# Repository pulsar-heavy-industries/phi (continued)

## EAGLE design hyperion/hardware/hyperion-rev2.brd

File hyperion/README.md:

# Hyperion

This repository contains the source code, Ableton remote script and hardware design for the Pulsar Heavy Industries Hyperion module.

Each Hyperion module provides you with:
* Fader.
* 2 Pressable rotary encoders.
* 7 Pots with center detent.
* 8 LED-lit pushbuttons - 2 blue and 6 red/green(/orange).
* 2 color OLED display.
* Standard PHI CANBUS connectivity.
* A powerful [STM32F405](http://www.st.com/en/microcontrollers/stm32f405-415.html?querycriteria=productId=LN1035) microcontroller.
* 10 segment (7 green + 3 red) LED bar graph.

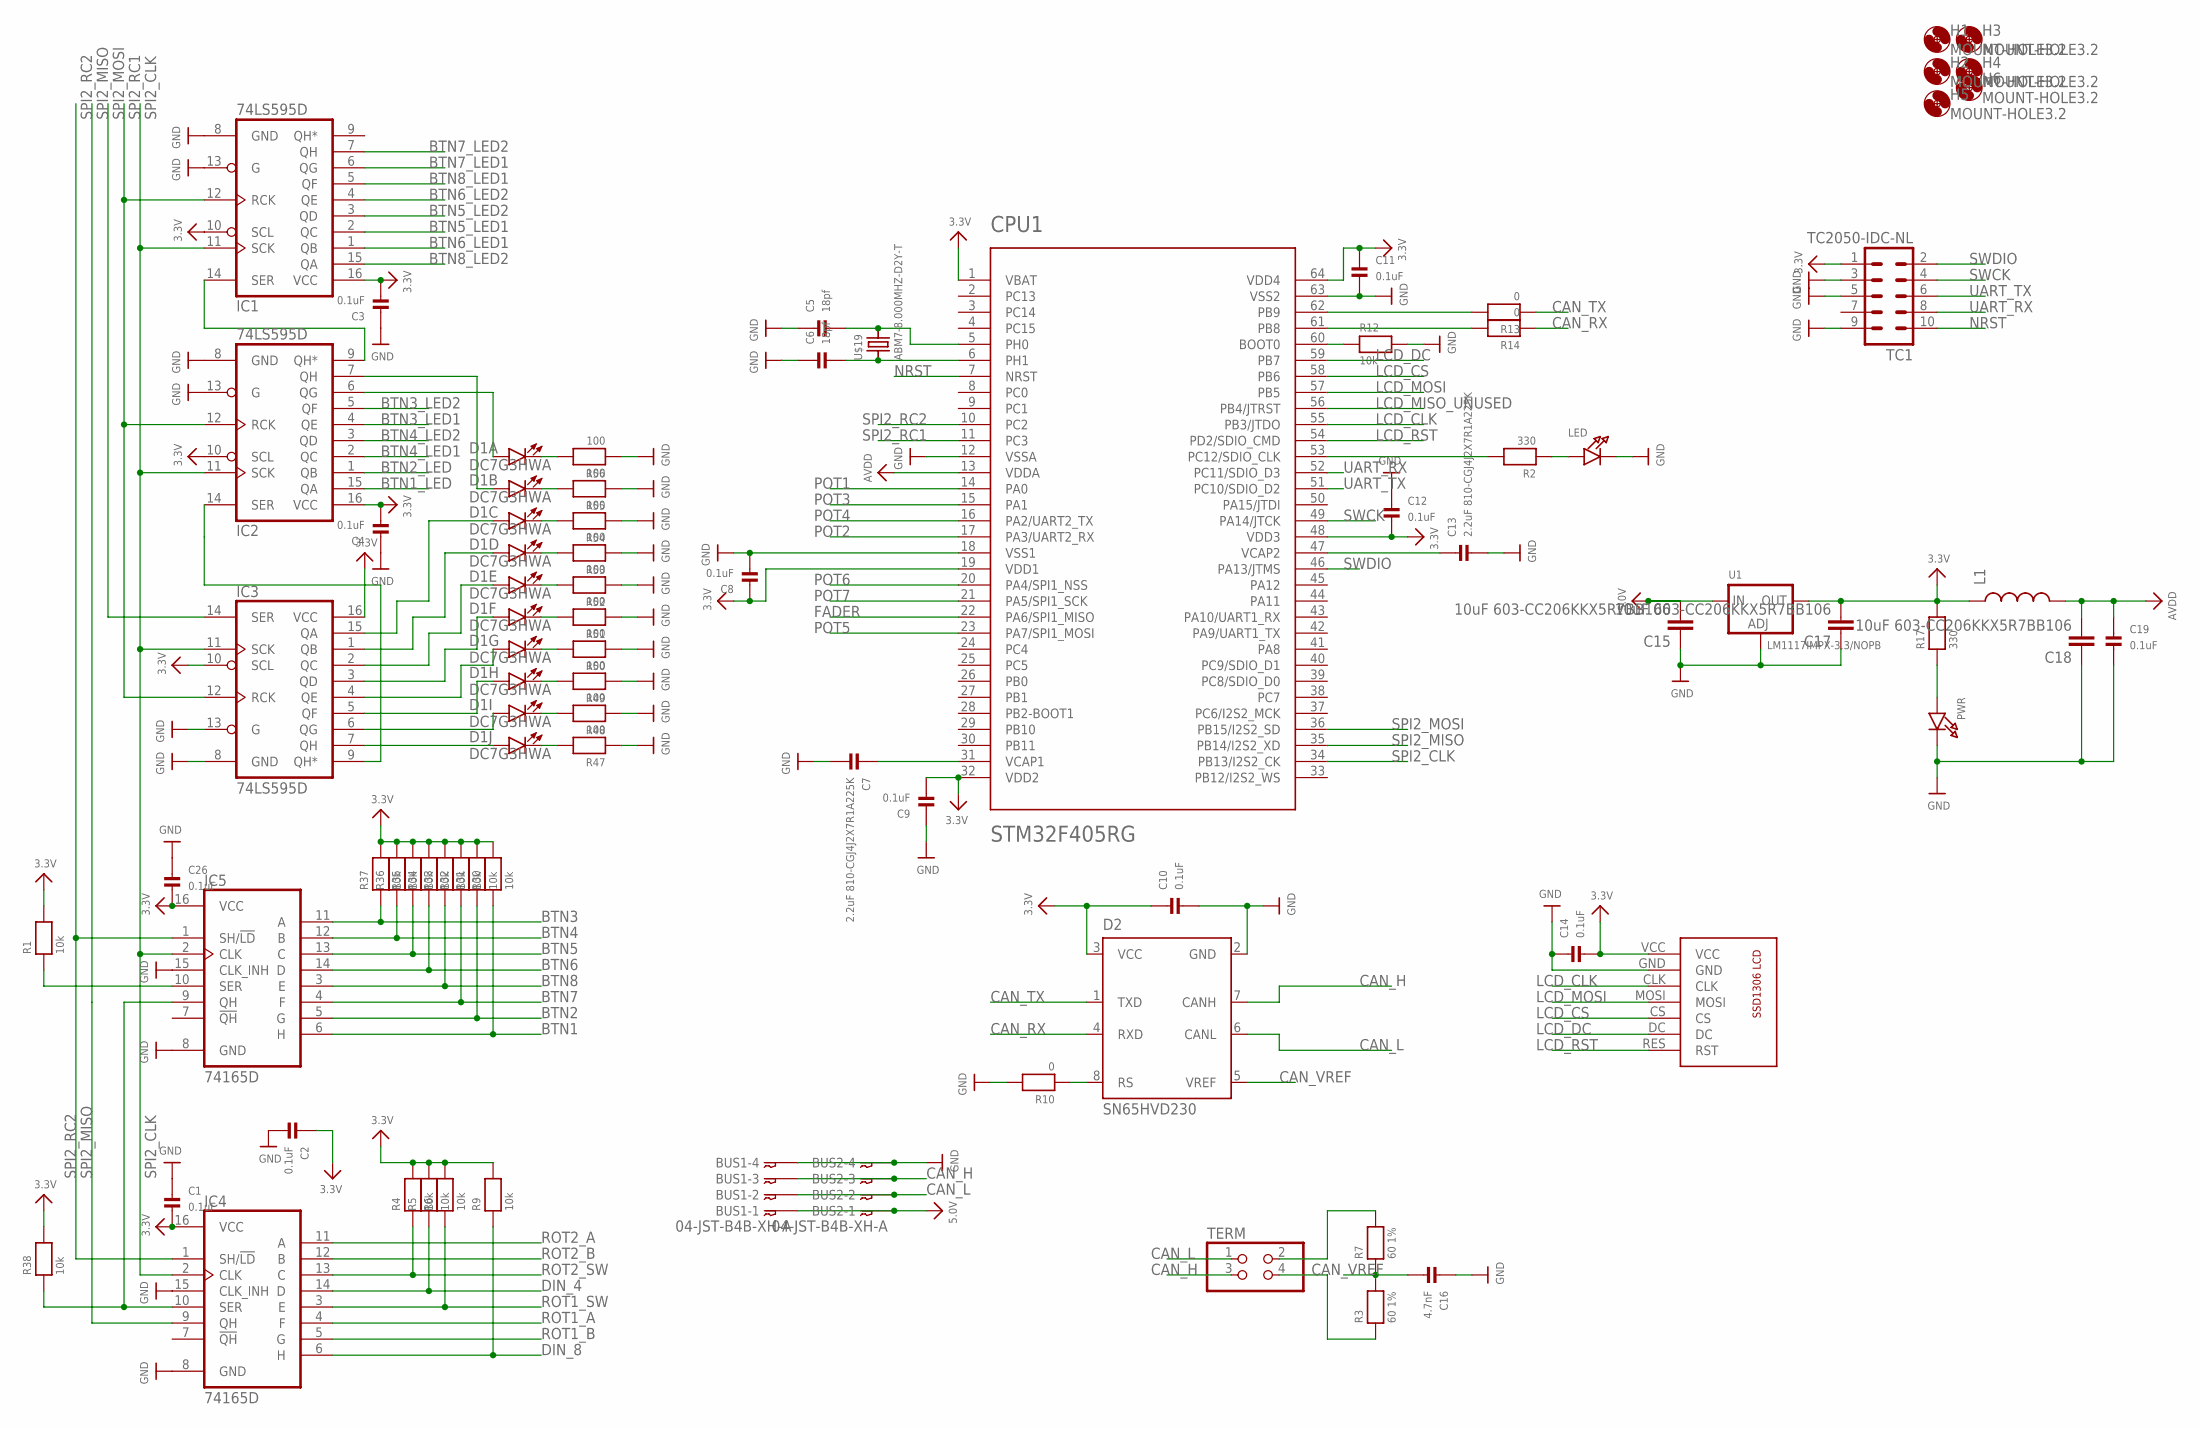
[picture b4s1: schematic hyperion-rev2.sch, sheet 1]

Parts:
BUS1, BUS2: 04-JST-B4B-XH-A; B4B-XH
C1, C2, C3, C4, C8, C9, C10, C11, C12, C14, C19, C26: 0.1uF; 0603
C5, C6: 18pf; 0603
C7, C13: 2.2uF 810-CGJ4J2X7R1A225K; 0805; MPN CGJ4J2X7R1A225K125AA
C15, C17, C18: 10uF 603-CC206KKX5R7BB106; 1206; MPN CC1206KKX5R7BB106
C16: 4.7nF; 0603
CPU1: STM32F405RG; TQFP64; MPN STM32F405RGT6
D1: DC7G3HWA; LED_BARGAPH_10
D2: SN65HVD230; SO8
H1, H2, H3, H4, H5, H6: MOUNT-HOLE3.2; 3,2
IC1, IC2, IC3: 74LS595D; SO16
IC4, IC5: 74165D; SO16
L1: INDUCTOR0805; 0805; MPN 2508056017Y2
LCD: SSD1306-7PINWITHOUT-HOLES; SSD1306-7PIN-NO-HOLES
LED: LED0603; CHIPLED_0603
PWR: LED0603; CHIPLED_0603
R1, R4, R5, R6, R9, R12, R30, R31, R32, R33, R34, R35, R36, R37, R38: 10k; _0603
R2, R17: 330; 0603
R3, R7: 60 1%; 0603; MPN MF-RES-0603-60.4
R10, R13, R14: 0; _0603
R47, R48, R49, R50, R51, R52, R53, R54, R55, R56: 100; _0603
TC1: TC2050-IDC-NL
TERM: PINHD-2X2; 2X02
U1: LM1117IMPX-3.3/NOPB; SOT223-R
U$19: ABM7-8.000MHZ-D2Y-T

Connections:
3.3V: C1.2, C2.1, C3.2, C4.2, C8.1, C9.2, C10.1, C11.1, C12.2, C14.2, C17.2, C26.2, CPU1.1 (VBAT), CPU1.19 (VDD1), CPU1.32 (VDD2), CPU1.48 (VDD3), CPU1.64 (VDD4), D2.3 (VCC), IC1.10 (SCL), IC1.16 (VCC), IC2.10 (SCL), IC2.16 (VCC), IC3.10 (SCL), IC3.16 (VCC), IC4.16 (VCC), IC5.16 (VCC), L1.1, LCD.VCC, R1.2, R4.2, R5.2, R6.2, R9.2, R17.2, R30.2, R31.2, R32.2, R33.2, R34.2, R35.2, R36.2, R37.2, R38.2, TC1.1, U1.2 (OUT); also elsewhere on the board
5.0V: BUS1.P$1, BUS2.P$1, C15.2, U1.3 (IN); also elsewhere on the board
AVDD: C18.2, C19.1, CPU1.13 (VDDA), L1.2
BTN1: IC5.6 (H), R30.1; also elsewhere on the board
BTN1_LED: IC2.15 (QA); also elsewhere on the board
BTN2: IC5.5 (G), R31.1; also elsewhere on the board
BTN2_LED: IC2.1 (QB); also elsewhere on the board
BTN3: IC5.11 (A), R37.1; also elsewhere on the board
BTN3_LED1: IC2.4 (QE); also elsewhere on the board
BTN3_LED2: IC2.5 (QF); also elsewhere on the board
BTN4: IC5.12 (B), R36.1; also elsewhere on the board
BTN4_LED1: IC2.2 (QC); also elsewhere on the board
BTN4_LED2: IC2.3 (QD); also elsewhere on the board
BTN5: IC5.13 (C), R35.1; also elsewhere on the board
BTN5_LED1: IC1.2 (QC); also elsewhere on the board
BTN5_LED2: IC1.3 (QD); also elsewhere on the board
BTN6: IC5.14 (D), R34.1; also elsewhere on the board
BTN6_LED1: IC1.1 (QB); also elsewhere on the board
BTN6_LED2: IC1.4 (QE); also elsewhere on the board
BTN7: IC5.4 (F), R32.1; also elsewhere on the board
BTN7_LED1: IC1.6 (QG); also elsewhere on the board
BTN7_LED2: IC1.7 (QH); also elsewhere on the board
BTN8: IC5.3 (E), R33.1; also elsewhere on the board
BTN8_LED1: IC1.5 (QF); also elsewhere on the board
BTN8_LED2: IC1.15 (QA); also elsewhere on the board
CAN_H: BUS1.P$3, BUS2.P$3, D2.7 (CANH), TERM.3
CAN_L: BUS1.P$2, BUS2.P$2, D2.6 (CANL), TERM.1
CAN_RX: D2.4 (RXD), R14.1
CAN_TX: D2.1 (TXD), R13.1
CAN_VREF: C16.2, D2.5 (VREF), R3.2, R7.1
DIN_4: IC4.14 (D), R5.1
DIN_8: IC4.6 (H), R9.1
FADER: CPU1.22 (PA6/SPI1_MISO); also elsewhere on the board
GND: BUS1.P$4, BUS2.P$4, C1.1, C2.2, C3.1, C4.1, C5.1, C6.1, C7.2, C8.2, C9.1, C10.2, C11.2, C12.1, C13.2, C14.1, C15.1, C16.1, C17.1, C18.1, C19.2, C26.1, CPU1.12 (VSSA), CPU1.18 (VSS1), CPU1.63 (VSS2), D2.2 (GND), IC1.8 (GND), IC1.13 (G), IC2.8 (GND), IC2.13 (G), IC3.8 (GND), IC3.13 (G), IC4.8 (GND), IC4.15 (CLK_INH), IC5.8 (GND), IC5.15 (CLK_INH), LCD.GND, LED.C, PWR.C, R10.2, R12.2, R47.1, R48.1, R49.1, R50.1, R51.1, R52.1, R53.1, R54.1, R55.1, R56.1, TC1.3, TC1.5, TC1.9, U1.1 (ADJ); also elsewhere on the board
LCD_CLK: CPU1.55 (PB3/JTDO), LCD.CLK
LCD_CS: CPU1.58 (PB6), LCD.CS
LCD_DC: CPU1.59 (PB7), LCD.DC
LCD_MISO_UNUSED: CPU1.56 (PB4/JTRST)
LCD_MOSI: CPU1.57 (PB5), LCD.MOSI
LCD_RST: CPU1.54 (PD2/SDIO_CMD), LCD.RES (RST)
unnamed: C6.2, CPU1.6 (PH1), U$19.P$1 (1)
unnamed: C5.2, CPU1.5 (PH0), U$19.P$2 (2)
unnamed: C13.1, CPU1.47 (VCAP2)
unnamed: C7.1, CPU1.31 (VCAP1)
unnamed: PWR.A, R17.1
unnamed: CPU1.60 (BOOT0), R12.1
unnamed: D1.5 (A), IC3.2 (QC)
unnamed: D1.2 (A), IC2.7 (QH)
unnamed: D1.1 (A), IC2.6 (QG)
unnamed: IC1.14 (SER), IC2.9 (QH*)
unnamed: CPU1.62 (PB9), R13.2
unnamed: D1.11 (C), R47.2
unnamed: D1.12 (C), R48.2
unnamed: D1.13 (C), R49.2
unnamed: D1.14 (C), R50.2
unnamed: D1.15 (C), R51.2
unnamed: D1.16 (C), R52.2
unnamed: D1.17 (C), R53.2
unnamed: D1.18 (C), R54.2
unnamed: D1.19 (C), R55.2
unnamed: D1.20 (C), R56.2
unnamed: IC4.10 (SER), IC5.9 (QH), R38.1
unnamed: CPU1.61 (PB8), R14.2
unnamed: IC5.10 (SER), R1.1
unnamed: LED.A, R2.1
unnamed: D1.10 (A), IC3.7 (QH)
unnamed: D1.9 (A), IC3.6 (QG)
unnamed: D1.8 (A), IC3.5 (QF)
unnamed: CPU1.53 (PC12/SDIO_CLK), R2.2
unnamed: R7.2, TERM.2
unnamed: R3.1, TERM.4
unnamed: D1.7 (A), IC3.4 (QE)
unnamed: D1.6 (A), IC3.3 (QD)
unnamed: D1.4 (A), IC3.1 (QB)
unnamed: D1.3 (A), IC3.15 (QA)
unnamed: IC2.14 (SER), IC3.9 (QH*)
unnamed: D2.8 (RS), R10.1
NRST: CPU1.7 (NRST), TC1.10
POT1: CPU1.14 (PA0); also elsewhere on the board
POT2: CPU1.17 (PA3/UART2_RX); also elsewhere on the board
POT3: CPU1.15 (PA1); also elsewhere on the board
POT4: CPU1.16 (PA2/UART2_TX); also elsewhere on the board
POT5: CPU1.23 (PA7/SPI1_MOSI); also elsewhere on the board
POT6: CPU1.20 (PA4/SPI1_NSS); also elsewhere on the board
POT7: CPU1.21 (PA5/SPI1_SCK); also elsewhere on the board
ROT1_A: IC4.4 (F); also elsewhere on the board
ROT1_B: IC4.5 (G); also elsewhere on the board
ROT1_SW: IC4.3 (E), R6.1; also elsewhere on the board
ROT2_A: IC4.11 (A); also elsewhere on the board
ROT2_B: IC4.12 (B); also elsewhere on the board
ROT2_SW: IC4.13 (C), R4.1; also elsewhere on the board
SPI2_CLK: CPU1.34 (PB13/I2S2_CK), IC1.11 (SCK), IC2.11 (SCK), IC3.11 (SCK), IC4.2 (CLK), IC5.2 (CLK)
SPI2_MISO: CPU1.35 (PB14/I2S2_XD), IC4.9 (QH)
SPI2_MOSI: CPU1.36 (PB15/I2S2_SD), IC3.14 (SER)
SPI2_RC1: CPU1.11 (PC3), IC1.12 (RCK), IC2.12 (RCK), IC3.12 (RCK)
SPI2_RC2: CPU1.10 (PC2), IC4.1 (SH/!LD), IC5.1 (SH/!LD)
SWCK: CPU1.49 (PA14/JTCK), TC1.4
SWDIO: CPU1.46 (PA13/JTMS), TC1.2
UART_RX: CPU1.52 (PC11/SDIO_D3), TC1.8
UART_TX: CPU1.51 (PC10/SDIO_D2), TC1.6

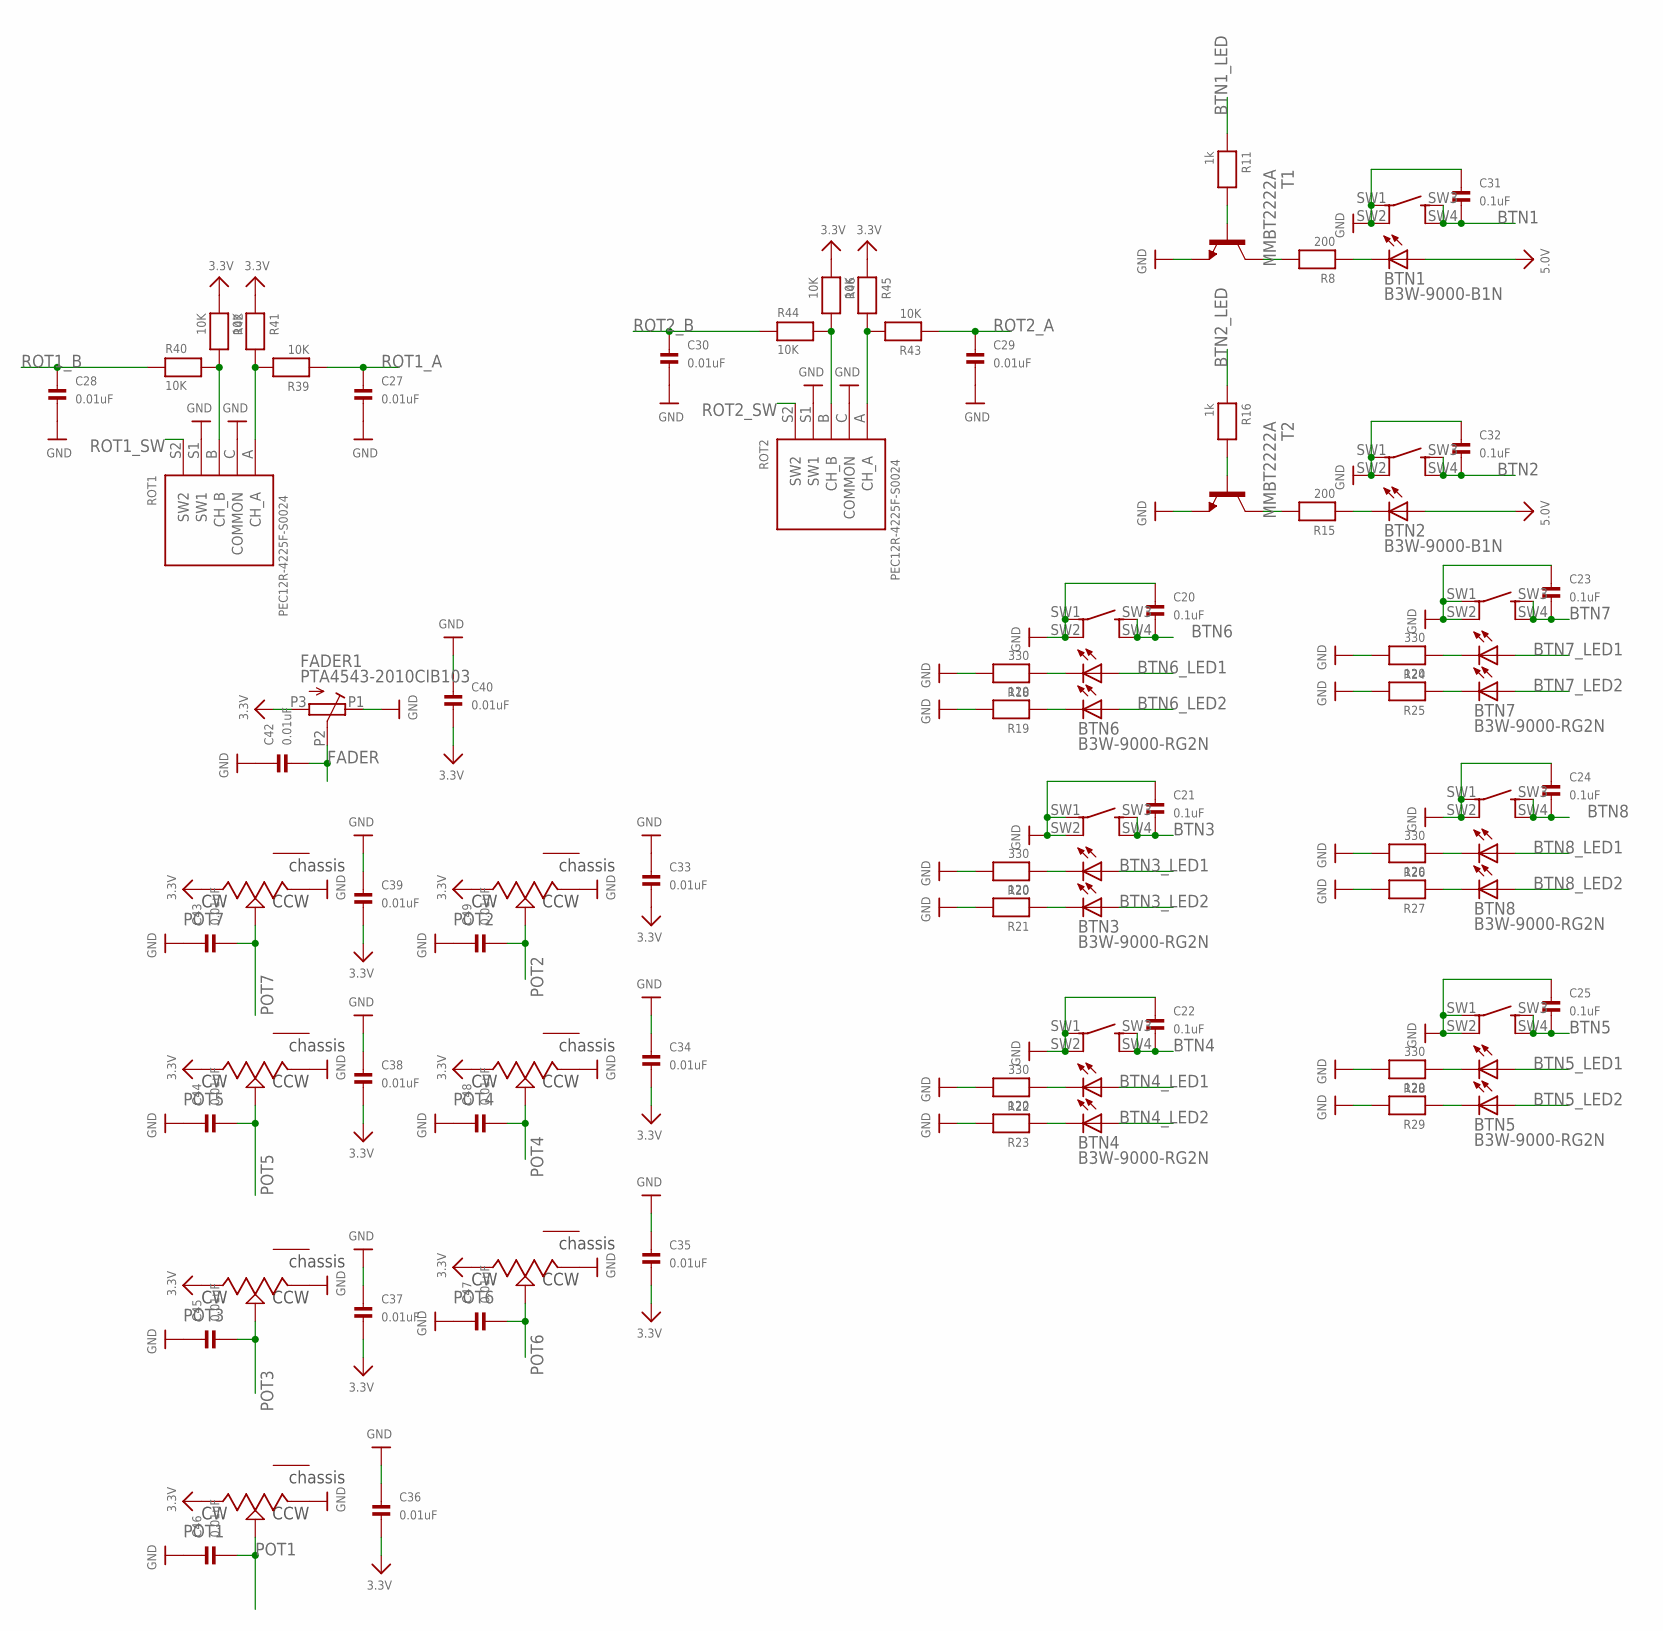
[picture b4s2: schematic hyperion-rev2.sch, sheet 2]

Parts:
BTN1, BTN2: B3W-9000-B1N; B3W-9000-X1X
BTN3, BTN4, BTN5, BTN6, BTN7, BTN8: B3W-9000-RG2N; B3W-9000-X2X
C20, C21, C22, C23, C24, C25, C31, C32: 0.1uF; 0603
C27, C28, C29, C30, C33, C34, C35, C36, C37, C38, C39, C40, C42, C43, C44, C45, C46, C47, C48, C49: 0.01uF; 0603
FADER1: PTA4543-2010CIB103; PTA4543-2015CPB103
POT1, POT2, POT3, POT4, POT5, POT6, POT7: POTENTIOMETERPTV09A_VERTICAL; PTV09A-4
R8, R15: 200; 0603
R11, R16: 1k; 0603
R18, R20, R22, R24, R26, R28: 330; 0603
R19, R21, R23, R25, R27, R29: 120; 0603
R39, R40, R41, R42, R43, R44, R45, R46: 10K; 0603
ROT1, ROT2: PEC12R-4225F-S0024; PEC111-4XXXK-SXXXX
T1, T2: MMBT2222A; SOT23-BEC

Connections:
3.3V: C33.2, C34.2, C35.2, C36.2, C37.2, C38.2, C39.2, C40.2, FADER1.P3 (E), POT1.CW, POT2.CW, POT3.CW, POT4.CW, POT5.CW, POT6.CW, POT7.CW, R41.1, R42.1, R45.1, R46.1; also elsewhere on the board
5.0V: BTN1.LED1+, BTN2.LED1+; also elsewhere on the board
BTN1: BTN1.SW3 (SW2_A), BTN1.SW4 (SW2_B), C31.2; also elsewhere on the board
BTN1_LED: R11.1; also elsewhere on the board
BTN2: BTN2.SW3 (SW2_A), BTN2.SW4 (SW2_B), C32.2; also elsewhere on the board
BTN2_LED: R16.1; also elsewhere on the board
BTN3: BTN3.SW3 (SW2_A), BTN3.SW4 (SW2_B), C21.2; also elsewhere on the board
BTN3_LED1: BTN3.LED1+; also elsewhere on the board
BTN3_LED2: BTN3.LED2+; also elsewhere on the board
BTN4: BTN4.SW3 (SW2_A), BTN4.SW4 (SW2_B), C22.2; also elsewhere on the board
BTN4_LED1: BTN4.LED1+; also elsewhere on the board
BTN4_LED2: BTN4.LED2+; also elsewhere on the board
BTN5: BTN5.SW3 (SW2_A), BTN5.SW4 (SW2_B), C25.2; also elsewhere on the board
BTN5_LED1: BTN5.LED1+; also elsewhere on the board
BTN5_LED2: BTN5.LED2+; also elsewhere on the board
BTN6: BTN6.SW3 (SW2_A), BTN6.SW4 (SW2_B), C20.2; also elsewhere on the board
BTN6_LED1: BTN6.LED1+; also elsewhere on the board
BTN6_LED2: BTN6.LED2+; also elsewhere on the board
BTN7: BTN7.SW3 (SW2_A), BTN7.SW4 (SW2_B), C23.2; also elsewhere on the board
BTN7_LED1: BTN7.LED1+; also elsewhere on the board
BTN7_LED2: BTN7.LED2+; also elsewhere on the board
BTN8: BTN8.SW3 (SW2_A), BTN8.SW4 (SW2_B), C24.2; also elsewhere on the board
BTN8_LED1: BTN8.LED1+; also elsewhere on the board
BTN8_LED2: BTN8.LED2+; also elsewhere on the board
FADER: C42.2, FADER1.P2 (S); also elsewhere on the board
GND: BTN1.SW1 (SW1_A), BTN1.SW2 (SW1_B), BTN2.SW1 (SW1_A), BTN2.SW2 (SW1_B), BTN3.SW1 (SW1_A), BTN3.SW2 (SW1_B), BTN4.SW1 (SW1_A), BTN4.SW2 (SW1_B), BTN5.SW1 (SW1_A), BTN5.SW2 (SW1_B), BTN6.SW1 (SW1_A), BTN6.SW2 (SW1_B), BTN7.SW1 (SW1_A), BTN7.SW2 (SW1_B), BTN8.SW1 (SW1_A), BTN8.SW2 (SW1_B), C20.1, C21.1, C22.1, C23.1, C24.1, C25.1, C27.2, C28.2, C29.2, C30.2, C31.1, C32.1, C33.1, C34.1, C35.1, C36.1, C37.1, C38.1, C39.1, C40.1, C42.1, C43.1, C44.1, C45.1, C46.1, C47.1, C48.1, C49.1, FADER1.P1 (A), POT1.CCW, POT2.CCW, POT3.CCW, POT4.CCW, POT5.CCW, POT6.CCW, POT7.CCW, R18.2, R19.2, R20.2, R21.2, R22.2, R23.2, R24.2, R25.2, R26.2, R27.2, R28.2, R29.2, ROT1.C (COMMON), ROT1.S1 (SW1), ROT2.C (COMMON), ROT2.S1 (SW1), T1.E, T2.E; also elsewhere on the board
unnamed: BTN6.LED1-, R18.1
unnamed: BTN6.LED2-, R19.1
unnamed: BTN3.LED1-, R20.1
unnamed: BTN3.LED2-, R21.1
unnamed: BTN7.LED1-, R24.1
unnamed: BTN7.LED2-, R25.1
unnamed: R40.2, R42.2, ROT1.B (CH_B)
unnamed: R39.2, R41.2, ROT1.A (CH_A)
unnamed: BTN8.LED1-, R26.1
unnamed: BTN8.LED2-, R27.1
unnamed: R44.2, R46.2, ROT2.B (CH_B)
unnamed: R43.2, R45.2, ROT2.A (CH_A)
unnamed: BTN4.LED1-, R22.1
unnamed: BTN4.LED2-, R23.1
unnamed: BTN5.LED1-, R28.1
unnamed: BTN5.LED2-, R29.1
unnamed: BTN2.LED1-, R15.1
unnamed: BTN1.LED1-, R8.1
unnamed: R8.2, T1.C
unnamed: R11.2, T1.B
unnamed: R15.2, T2.C
unnamed: R16.2, T2.B
POT1: C46.2, POT1.CENTER (WIPER); also elsewhere on the board
POT2: C49.2, POT2.CENTER (WIPER); also elsewhere on the board
POT3: C45.2, POT3.CENTER (WIPER); also elsewhere on the board
POT4: C48.2, POT4.CENTER (WIPER); also elsewhere on the board
POT5: C44.2, POT5.CENTER (WIPER); also elsewhere on the board
POT6: C47.2, POT6.CENTER (WIPER); also elsewhere on the board
POT7: C43.2, POT7.CENTER (WIPER); also elsewhere on the board
ROT1_A: C27.1, R39.1; also elsewhere on the board
ROT1_B: C28.1, R40.1; also elsewhere on the board
ROT1_SW: ROT1.S2 (SW2); also elsewhere on the board
ROT2_A: C29.1, R43.1; also elsewhere on the board
ROT2_B: C30.1, R44.1; also elsewhere on the board
ROT2_SW: ROT2.S2 (SW2); also elsewhere on the board

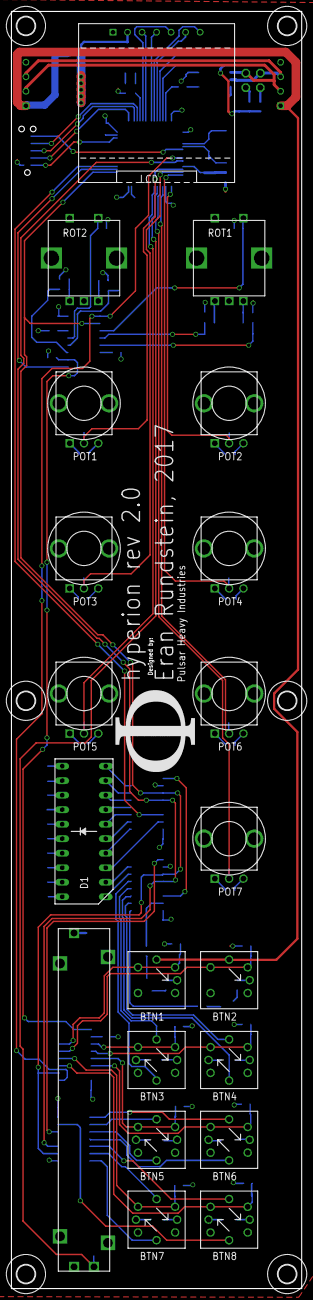
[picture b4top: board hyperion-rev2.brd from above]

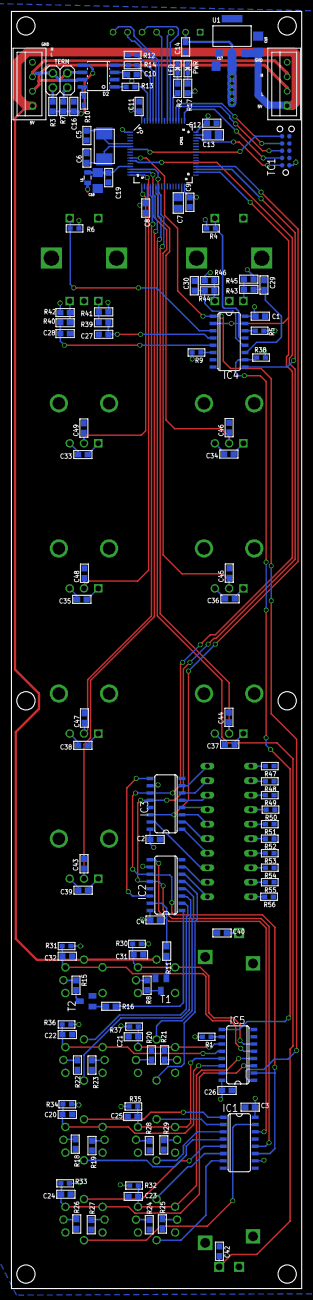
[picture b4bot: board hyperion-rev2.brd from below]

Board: 2 copper layers, 50.8 x 223.5 mm, 148 parts (122 on the bottom side), 121 nets.

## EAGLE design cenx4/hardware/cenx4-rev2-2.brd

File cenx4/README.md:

# Cenx4

This repository contains the source code, Ableton remote script and hardware design for the Pulsar Heavy Industries Cenx4 controller.

The main features are (some of which are already fully implemented):
- Easy to use: Automatic mapping of selected device's parameters (as seen in the image below). Getting this to work requires almost no setup and no manual mapping in Ableton (just selecting the right remote script).
- Modular: The thing you see is actually two modules connected togeter using [CAN bus](https://en.wikipedia.org/wiki/CAN_bus).
- Updateable: Support firmware update over MIDI and over CAN. The master unit takes care of updating the slaves automatically.
- Open source: Can be used as a basis for many other controllers.

I am still in the process in documenting everything, but please refer to the following posts for more information:

[DIY Music Machines - Introduction](https://blog.rundste.in/2016/12/08/diy-music-machines-introduction/)

[DIY Music Machines - Ableton Live Controller Update](https://blog.rundste.in/2017/03/05/diy-music-machines-ableton-live-controller-update/)

# Basic steps in getting this to run

## Hardware
 - You will need the following:
   - A JTAG adapter compatible with openocd/gdb. I use an [STM32F4DISCOVERY](http://www.st.com/en/evaluation-tools/stm32f4discovery.html) for this
   - A [Tag-Connect TC2050-IDC](http://www.tag-connect.com/TC2050-IDC) cable
   - A PHI Cenx4 board (TODO: create+link to board page)
- The pinout of the Debug cable is as following (see page 2 [here](http://www.tag-connect.com/Materials/TC2050-IDC%20Datasheet.pdf) for where pin 1 is on the flat cable):
   - VCC: Pin 1
   - GND: Pin 2
   - NRST: Pin 6
   - UART_RX: Pin 7 (currently unused)
   - UART_TX: Pin 8 (currently unused)
   - SWCLK: Pin 9
   - SWDIO: Pin 10
 - If using an [STM32F4DISCOVERY](http://www.st.com/en/evaluation-tools/stm32f4discovery.html) board as JTAG, remove the jumpers on CN3 (labeled "ST-LINK"), and connect the following to CN2 (labeled "SWD" - pin 1 marked with a dot):
   - 1: VCC (Pin 1 on TagConnect flat cable)
   - 2: SWCLK (Pin 9 on TagConnect flat cable)
   - 3: GND (Pin 2 on TagConnect flat cable))
   - 4: SWDIO (Pin 10 on TagConnect flat cable)
   - 5: NRST (Pin 6 on TagConnect flat cable)
   - 6: Unused
 - There is a tiny adapter board inside `misc/st-tag-adapter` that makes it easier. You can order it from [OSH Park](https://oshpark.com/shared_projects/iMHjB8kG).
 - You will need at least one Cenx4 in Master configuration - this means CAN terminator jumpers installed (labeled CAN_TERM) and a USB connector soldered on.

## Software
- Download and extract [ChibiOS 16.1.7](https://sourceforge.net/projects/chibios/files/ChibiOS_RT%20stable/Version%2016.1.7/ChibiOS_16.1.7.zip/download) into `vendor/`
- Download and extract [uGfx 2.7](https://community.ugfx.io/files/file/2-%C2%B5gfx-library/?do=download&csrfKey=8ae07e04e710333d9b25ed4ae016a4ba) info `vendor/`
- Make you you have a working [ARM toolchain](https://launchpad.net/gcc-arm-embedded) in your path
- Build the bootloader by running `make` inside `cenx4/firmware/bl`
- Start openocd by running `openocd -f stm32f4discovery-chibios.cfg` inside the `openocd` directory
- Use GDB to download the bootloader:
    ```
    % arm-none-eabi-gdb build/ch.elf
    GNU gdb (GNU Tools for ARM Embedded Processors) 7.10.1.20160616-cvs
    Copyright (C) 2015 Free Software Foundation, Inc.
    License GPLv3+: GNU GPL version 3 or later <http://gnu.org/licenses/gpl.html>
    ...
    Reading symbols from build/ch.elf...done.
    (gdb) target remote 127.0.0.1:3333
    Remote debugging using 127.0.0.1:3333
    0x00000000 in ?? ()
    (gdb) monitor reset init
    Unable to match requested speed 1000 kHz, using 950 kHz
    Unable to match requested speed 1000 kHz, using 950 kHz
    adapter speed: 950 kHz
    target state: halted
    target halted due to debug-request, current mode: Thread
    xPSR: 0x01000000 pc: 0x080001a0 msp: 0x20000400
    Unable to match requested speed 8000 kHz, using 4000 kHz
    Unable to match requested speed 8000 kHz, using 4000 kHz
    adapter speed: 4000 kHz
    (gdb) load
    Loading section startup, size 0x1a0 lma 0x8000000
    Loading section .text, size 0x9d84 lma 0x80001a0
    Loading section .data, size 0x4bc lma 0x8009f28
    Start address 0x80001a0, load size 41952
    Transfer rate: 22 KB/sec, 8390 bytes/write.
    (gdb) continue
    Continuing.
    ```
 - The bootloader should now be running.
 - TODO: Instructions on how to use it to load the firmware
 - Build the application by running `make` inside `cenx4/firmware/app`
 - Once again use gdb, similar to the bootloader but use the ELF file `build/bl-ch.elf` (unlike `build/ch.elf`, `bl-ch.elf` is in the format the bootloader expects, so your application would run even when not using the debugger)
 - Copy `cenx4/ableton/Cenx4` into Ableton's Remote Scripts directory. On Mac, this would be `/Applications/Ableton Live 9 Suite.app/Contents/App-Resources/MIDI Remote Scripts`.
 - Start Ableton, and configure the MIDI devide. Make sure to use the Cenx4 remote script.

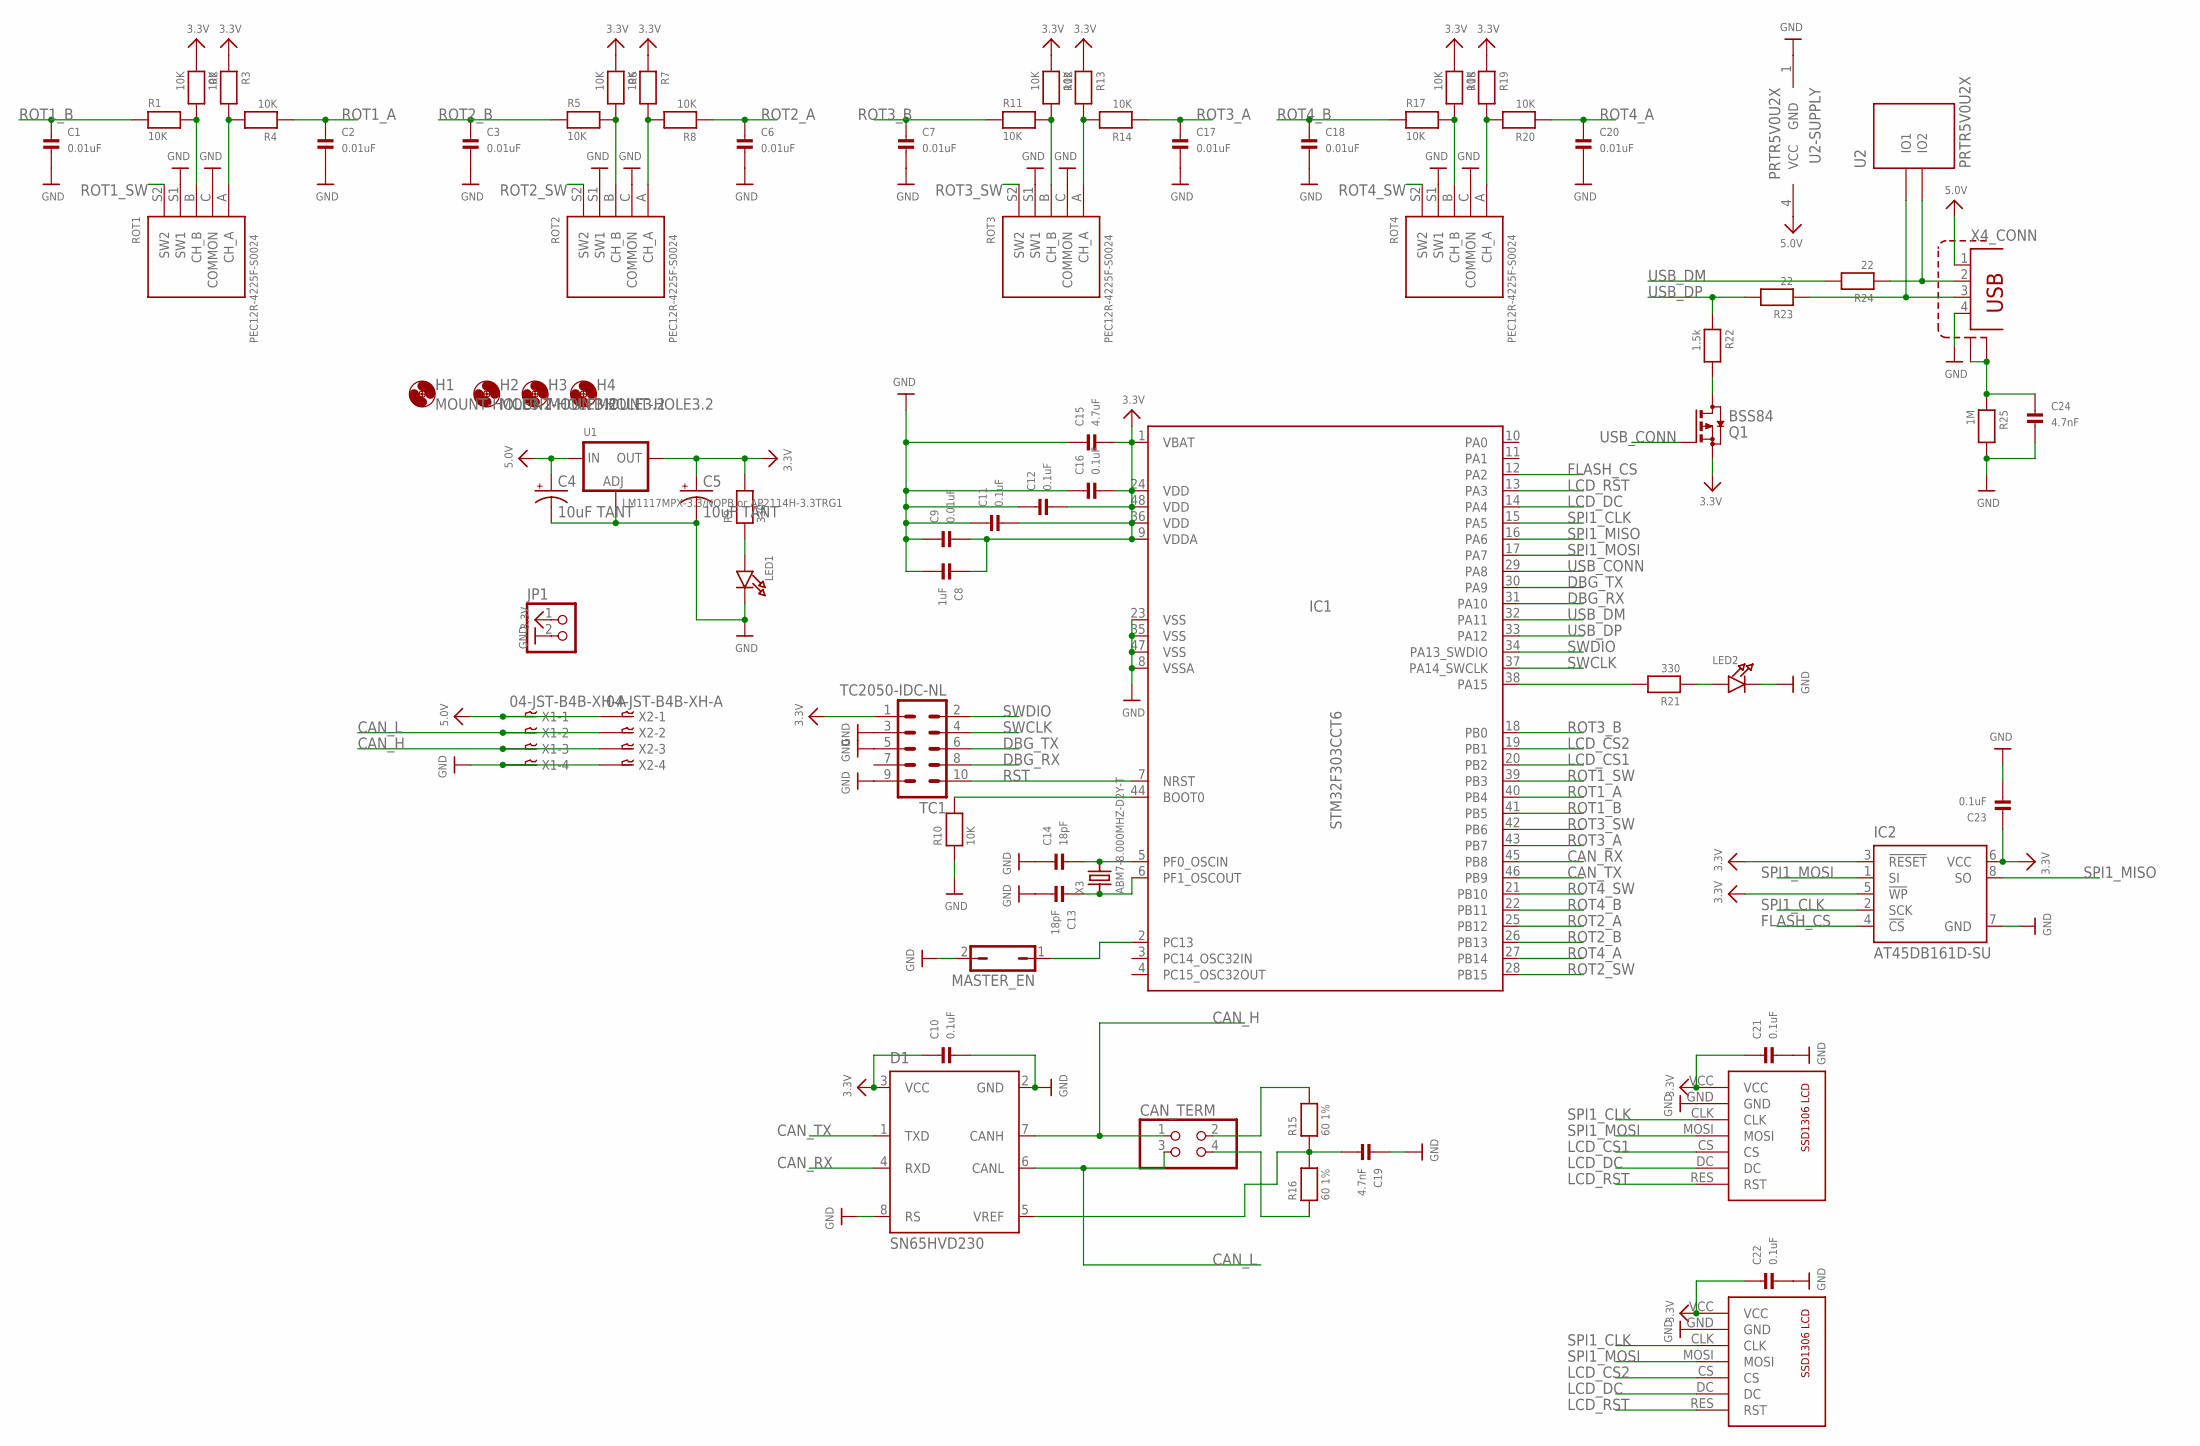
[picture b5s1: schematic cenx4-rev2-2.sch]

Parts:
C1, C2, C3, C6, C7, C9, C17, C18, C20: 0.01uF; 0603
C4, C5: 10uF TANT; 0603-POL
C8: 1uF; 0603
C10, C11, C12, C16, C21, C22, C23: 0.1uF; 0603
C13, C14: 18pF; 0603
C15: 4.7uF; 0603; MPN CL10A475MP5LNNC
C19, C24: 4.7nF; 0603
CAN_TERM: PINHD-2X2; 2X02
D1: SN65HVD230; SO8
H1, H2, H3, H4: MOUNT-HOLE3.2; 3,2
IC1: STM32F303CCT6; TQFP48
IC2: AT45DB161D-SU; 8S2
JP1: PINHD-1X2; 1X02
LCD1, LCD2: SSD1306-7PINWITHOUT-HOLES; SSD1306-7PIN-NO-HOLES
LED1, LED2: LED0603; CHIPLED_0603
MASTER_EN: JP1Q; JP1
Q1: BSS84; SOT23; MPN BSS84
R1, R2, R3, R4, R5, R6, R7, R8, R10, R11, R12, R13, R14, R17, R18, R19, R20: 10K; 0603
R9, R21: 330; 0603; MPN MF-RES-0603-330
R15, R16: 60 1%; 0603; MPN MF-RES-0603-60.4
R22: 1.5k; 0603; MPN MCR03ERTF1501
R23, R24: 22; 0603; MPN MF-RES-0603-22
R25: 1M; 0603
ROT1, ROT2, ROT3, ROT4: PEC12R-4225F-S0024; PEC111-4XXXK-SXXXX
TC1: TC2050-IDC-NL
U1: LM1117MPX-3.3/NOPB or AP2114H-3.3TRG1; SOT223-R
U2: PRTR5V0U2X; SOT-143B
X1, X2: 04-JST-B4B-XH-A; B4B-XH
X3: ABM7-8.000MHZ-D2Y-T
X4: TE-292304-1

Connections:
3.3V: C5.A (+), C8.1, C9.2, C10.1, C11.2, C12.2, C15.2, C16.2, C21.1, C22.1, C23.1, D1.3 (VCC), IC1.1 (VBAT), IC1.9 (VDDA), IC1.24 (VDD), IC1.36 (VDD), IC1.48 (VDD), IC2.3 (!RESET), IC2.5 (!WP), IC2.6 (VCC), JP1.1, LCD1.VCC, LCD2.VCC, Q1.2 (S), R2.1, R3.1, R6.1, R7.1, R9.2, R12.1, R13.1, R18.1, R19.1, TC1.1, U1.2 (OUT)
5.0V: C4.A (+), U1.3 (IN), U2.4 (VCC), X1.P$1, X2.P$1, X4.1
CAN_H: CAN_TERM.1, D1.7 (CANH), X1.P$3, X2.P$3
CAN_L: CAN_TERM.3, D1.6 (CANL), X1.P$2, X2.P$2
CAN_RX: D1.4 (RXD), IC1.45 (PB8)
CAN_TX: D1.1 (TXD), IC1.46 (PB9)
DBG_RX: IC1.31 (PA10), TC1.8
DBG_TX: IC1.30 (PA9), TC1.6
FLASH_CS: IC1.12 (PA2), IC2.4 (!CS)
GND: C1.2, C2.2, C3.2, C4.K (-), C5.K (-), C6.2, C7.2, C8.2, C9.1, C10.2, C11.1, C12.1, C13.2, C14.1, C15.1, C16.1, C17.2, C18.2, C19.1, C20.2, C21.2, C22.2, C23.2, C24.2, D1.2 (GND), D1.8 (RS), IC1.8 (VSSA), IC1.23 (VSS), IC1.35 (VSS), IC1.47 (VSS), IC2.7 (GND), JP1.2, LCD1.GND, LCD2.GND, LED1.C, LED2.C, MASTER_EN.2, R10.1, R25.2, ROT1.C (COMMON), ROT1.S1 (SW1), ROT2.C (COMMON), ROT2.S1 (SW1), ROT3.C (COMMON), ROT3.S1 (SW1), ROT4.C (COMMON), ROT4.S1 (SW1), TC1.3, TC1.5, TC1.9, U1.1 (ADJ), U2.1 (GND), X1.P$4, X2.P$4, X4.4
LCD_CS1: IC1.20 (PB2), LCD1.CS
LCD_CS2: IC1.19 (PB1), LCD2.CS
LCD_DC: IC1.14 (PA4), LCD1.DC, LCD2.DC
LCD_RST: IC1.13 (PA3), LCD1.RES (RST), LCD2.RES (RST)
unnamed: IC1.44 (BOOT0), R10.2
unnamed: C19.2, D1.5 (VREF), R15.1, R16.2
unnamed: LED1.A, R9.1
unnamed: CAN_TERM.2, R15.2
unnamed: CAN_TERM.4, R16.1
unnamed: IC1.38 (PA15), R21.2
unnamed: LED2.A, R21.1
unnamed: C14.2, IC1.5 (PF0_OSCIN), X3.P$2 (2)
unnamed: C13.1, IC1.6 (PF1_OSCOUT), X3.P$1 (1)
unnamed: R5.2, R6.2, ROT2.B (CH_B)
unnamed: R7.2, R8.2, ROT2.A (CH_A)
unnamed: R17.2, R18.2, ROT4.B (CH_B)
unnamed: R19.2, R20.2, ROT4.A (CH_A)
unnamed: R1.2, R2.2, ROT1.B (CH_B)
unnamed: R3.2, R4.2, ROT1.A (CH_A)
unnamed: R11.2, R12.2, ROT3.B (CH_B)
unnamed: R13.2, R14.2, ROT3.A (CH_A)
unnamed: R24.1, U2.3 (IO2), X4.2
unnamed: R23.1, U2.2 (IO1), X4.3
unnamed: C24.1, R25.1, X4.P$1 (S1), X4.P$2 (S2)
unnamed: Q1.3 (D), R22.2
unnamed: IC1.2 (PC13), MASTER_EN.1
ROT1_A: C2.1, IC1.40 (PB4), R4.1
ROT1_B: C1.1, IC1.41 (PB5), R1.1
ROT1_SW: IC1.39 (PB3), ROT1.S2 (SW2)
ROT2_A: C6.1, IC1.25 (PB12), R8.1
ROT2_B: C3.1, IC1.26 (PB13), R5.1
ROT2_SW: IC1.28 (PB15), ROT2.S2 (SW2)
ROT3_A: C17.1, IC1.43 (PB7), R14.1
ROT3_B: C7.1, IC1.18 (PB0), R11.1
ROT3_SW: IC1.42 (PB6), ROT3.S2 (SW2)
ROT4_A: C20.1, IC1.27 (PB14), R20.1
ROT4_B: C18.1, IC1.22 (PB11), R17.1
ROT4_SW: IC1.21 (PB10), ROT4.S2 (SW2)
RST: IC1.7 (NRST), TC1.10
SPI1_CLK: IC1.15 (PA5), IC2.2 (SCK), LCD1.CLK, LCD2.CLK
SPI1_MISO: IC1.16 (PA6), IC2.8 (SO)
SPI1_MOSI: IC1.17 (PA7), IC2.1 (SI), LCD1.MOSI, LCD2.MOSI
SWCLK: IC1.37 (PA14_SWCLK), TC1.4
SWDIO: IC1.34 (PA13_SWDIO), TC1.2
USB_CONN: IC1.29 (PA8), Q1.1 (G)
USB_DM: IC1.32 (PA11), R24.2
USB_DP: IC1.33 (PA12), R22.1, R23.2
